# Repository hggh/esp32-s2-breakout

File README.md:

# ESP 32 S2 breakout board

ESP32 S2 WROOM breakout board.

IO 18 is pulled high by R2 to ensure a correct ESP32 S2 startup.

breakout board has no LDO onboard to test low power applications with an external LDO or just use 3.3V from your USB ttl.

##### BOM

| number | name |
|---| ---|
| C1 | tantalum cap 220µF SMD EIA-7343-31 (Kemet-D) |
| C2 | ceramic cap 100 nF SMD 0805 |
| C3 | ceramic cap 0.1 µF SMD 0805 |
| R1,R2 | 10k SMD 0805 |
| U1 | ESP32-S2-WROOM |
| SW1 | SMD push switch  (opt.) |
| H1 | Pin Header for uploading |
| J1, J2, J3, J4 | pin header |

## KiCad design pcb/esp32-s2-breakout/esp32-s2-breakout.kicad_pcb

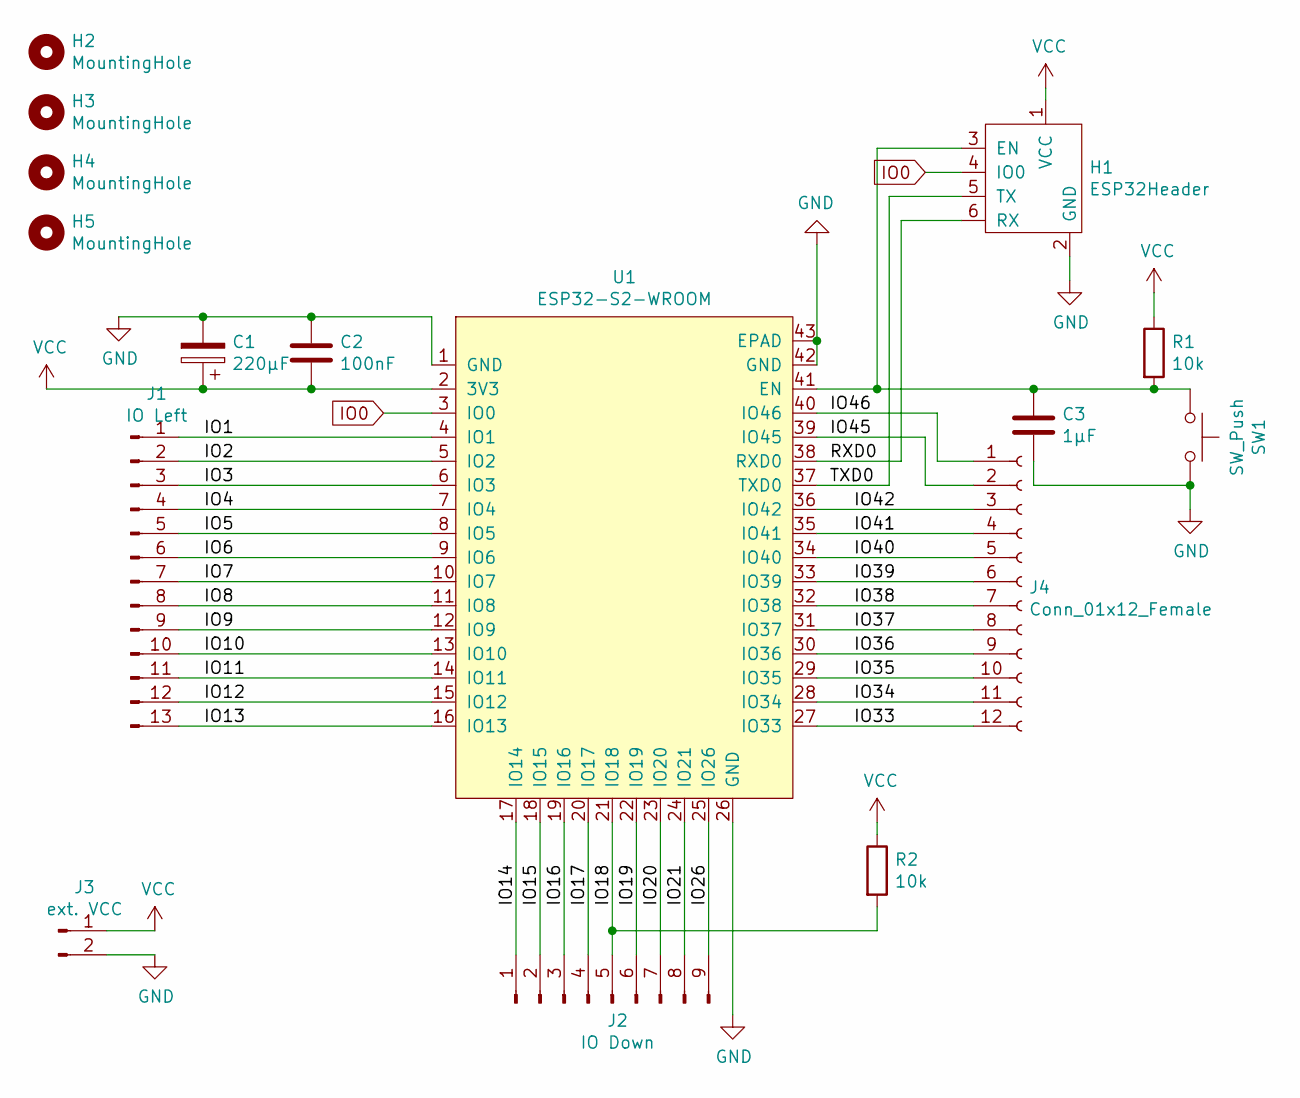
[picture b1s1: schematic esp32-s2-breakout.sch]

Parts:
C1: 220µF; CP_EIA-7343-31_Kemet-D
C2: 100nF; C_0805_2012Metric
C3: 1µF; C_0805_2012Metric
H1: ESP32Header; esp32-prog-header
H2, H3, H4, H5: MountingHole; MountingHole_3.2mm_M3
J1: IO Left; PinHeader_1x13_P2.54mm_Vertical
J2: IO Down; PinHeader_1x09_P2.54mm_Vertical
J3: ext. VCC; PinSocket_1x02_P2.54mm_Vertical
J4: Conn_01x12_Female; PinSocket_1x12_P2.54mm_Vertical
R1, R2: 10k; R_0805_2012Metric_Pad1.20x1.40mm_HandSolder
SW1: SW_Push; SMD_Button
U1: ESP32-S2-WROOM

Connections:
/IO1: J1.1, U1.4 (IO1)
/IO2: J1.2, U1.5 (IO2)
/IO3: J1.3, U1.6 (IO3)
/IO4: J1.4, U1.7 (IO4)
/IO5: J1.5, U1.8 (IO5)
/IO6: J1.6, U1.9 (IO6)
/IO7: J1.7, U1.10 (IO7)
/IO8: J1.8, U1.11 (IO8)
/IO9: J1.9, U1.12 (IO9)
/IO10: J1.10, U1.13 (IO10)
/IO11: J1.11, U1.14 (IO11)
/IO12: J1.12, U1.15 (IO12)
/IO13: J1.13, U1.16 (IO13)
/IO14: J2.1, U1.17 (IO14)
/IO15: J2.2, U1.18 (IO15)
/IO16: J2.3, U1.19 (IO16)
/IO17: J2.4, U1.20 (IO17)
/IO18: J2.5, R2.2, U1.21 (IO18)
/IO19: J2.6, U1.22 (IO19)
/IO20: J2.7, U1.23 (IO20)
/IO21: J2.8, U1.24 (IO21)
/IO26: J2.9, U1.25 (IO26)
/IO33: J4.12, U1.27 (IO33)
/IO34: J4.11, U1.28 (IO34)
/IO35: J4.10, U1.29 (IO35)
/IO36: J4.9, U1.30 (IO36)
/IO37: J4.8, U1.31 (IO37)
/IO38: J4.7, U1.32 (IO38)
/IO39: J4.6, U1.33 (IO39)
/IO40: J4.5, U1.34 (IO40)
/IO41: J4.4, U1.35 (IO41)
/IO42: J4.3, U1.36 (IO42)
/IO45: J4.2, U1.39 (IO45)
/IO46: J4.1, U1.40 (IO46)
/RXD0: H1.6 (RX), U1.38 (RXD0)
/TXD0: H1.5 (TX), U1.37 (TXD0)
GND: C1.2, C2.1, C3.2, H1.2 (GND), J3.2, SW1.2, U1.1 (GND), U1.26 (GND), U1.42 (GND), U1.43 (EPAD)
IO0: H1.4 (IO0), U1.3 (IO0)
unnamed: C3.1, H1.3 (EN), R1.2, SW1.1, U1.41 (EN)
VCC: C1.1, C2.2, H1.1 (VCC), J3.1, R1.1, R2.1, U1.2 (3V3)

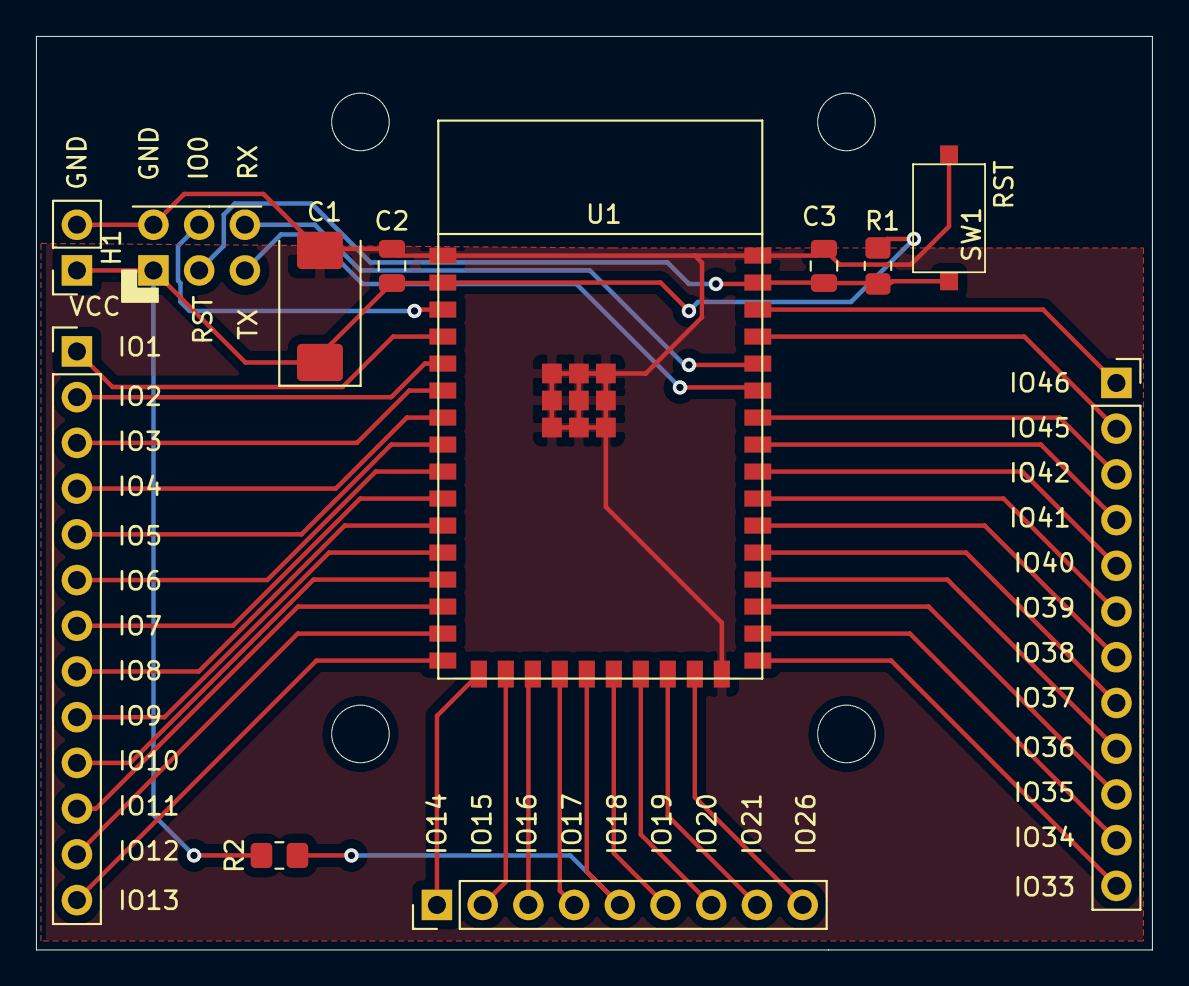
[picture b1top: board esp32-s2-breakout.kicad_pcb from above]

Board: 2 copper layers, 62.0 x 50.8 mm, 16 parts (0 on the bottom side), 40 nets.

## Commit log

2021-05-23 add breakout for ESP32-S2-WROOM
2021-05-25 add bom
